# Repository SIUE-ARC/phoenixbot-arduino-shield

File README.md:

# phoenixbot-arduino-shield
Arduino Shield Firmware

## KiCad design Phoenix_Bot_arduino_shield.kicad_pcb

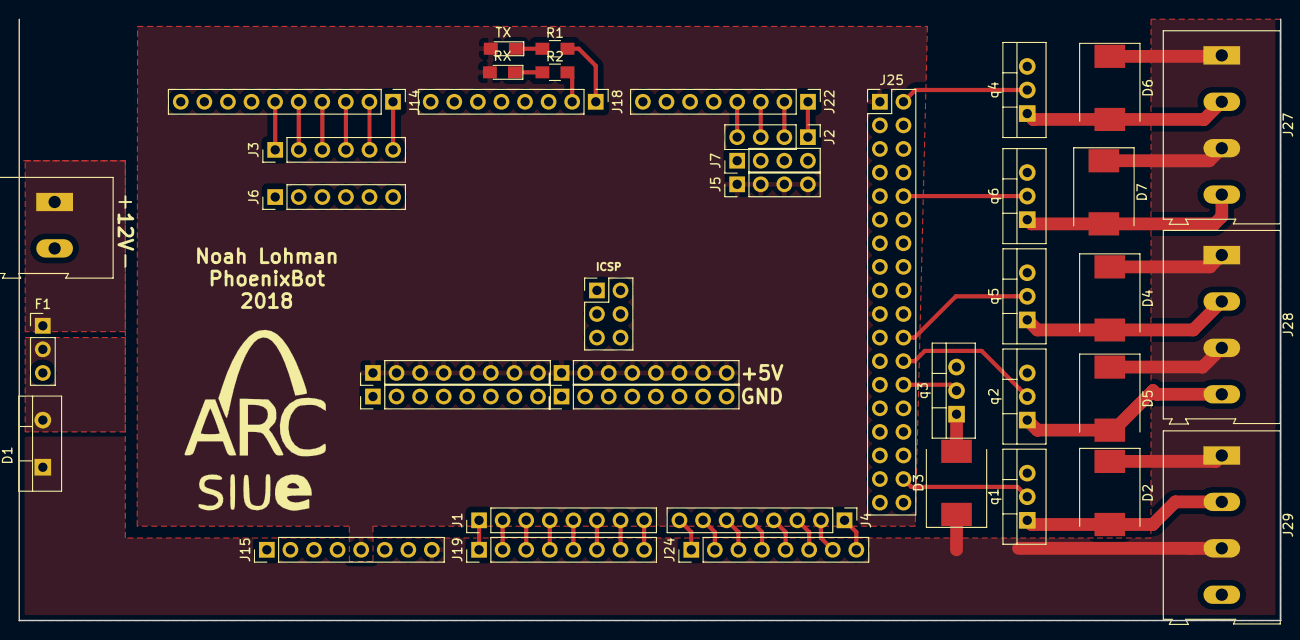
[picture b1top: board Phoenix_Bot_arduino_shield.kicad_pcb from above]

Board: 2 copper layers, 135.9 x 64.8 mm, 41 parts (0 on the bottom side), 48 nets.

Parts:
D1: D_Schottky; TO-220-2_Vertical
D2, D3, D4, D5, D6, D7: D_Schottky; D_SMC
D8: RX; LED_0805_HandSoldering
D9: TX; LED_0805_HandSoldering
F1: Fuse; Pin_Header_Straight_1x03_Pitch2.54mm
J1: Analog_signal_male; Pin_Header_Straight_1x08_Pitch2.54mm
J2: Encoder_Signal; Pin_Header_Straight_1x04_Pitch2.54mm
J3: Servo_signal; Pin_Header_Straight_1x06_Pitch2.54mm
J4: Analog_signal_female; Pin_Header_Straight_1x08_Pitch2.54mm
J5: encoder_power; Pin_Header_Straight_1x04_Pitch2.54mm
J6: Servo_ground; Pin_Header_Straight_1x06_Pitch2.54mm
J7: encoder_ground; Pin_Header_Straight_1x04_Pitch2.54mm
J8: 12V_terminal; TerminalBlock_Altech_AK300-2_P5.00mm
J14: PWN(10-5); Pin_Header_Straight_1x10_Pitch2.54mm
J15: On Board Supply; Pin_Header_Straight_1x08_Pitch2.54mm
J16, J17: 1x8 Male; Pin_Header_Straight_1x08_Pitch2.54mm
J18: PWM_(6-1); Pin_Header_Straight_1x08_Pitch2.54mm
J19: Analog_Pin_1; Pin_Header_Straight_1x08_Pitch2.54mm
J20, J21: 1x8 Female; Pin_Header_Straight_1x08_Pitch2.54mm
J22: Serial; Pin_Header_Straight_1x08_Pitch2.54mm
J23: ICSP; Pin_Header_Straight_2x03_Pitch2.54mm
J24: Analog_Pin_2; Pin_Header_Straight_1x08_Pitch2.54mm
J25: Digital_Pins; Pin_Header_Straight_2x18_Pitch2.54mm
J27: Solenoid_terminal; TerminalBlock_Altech_AK300-4_P5.00mm
J28: Solendoid_middle_terminal; TerminalBlock_Altech_AK300-4_P5.00mm
J29: bottom_solenoid_terminal; TerminalBlock_Altech_AK300-4_P5.00mm
R1, R2: R; R_0805_HandSoldering
q1: solenoid_1; TO-220-3_Vertical
q2: solenoid_4; TO-220-3_Vertical
q3, q5: solenoid_3; TO-220-3_Vertical
q4: solenoid_5; TO-220-3_Vertical
q6: solenoid_6; TO-220-3_Vertical

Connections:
+5V: D8.2, D9.2, J5.1, J5.2, J5.3, J5.4, J15.5, J17.1, J17.2, J17.3, J17.4, J17.5, J17.6, J17.7, J17.8, J20.1, J20.2, J20.3, J20.4, J20.5, J20.6, J20.7, J20.8, J25.1, J25.19
+12V: D1.1, D2.1, D3.1, D4.1, D5.1, D6.1, D7.1, J15.8, J27.1, J27.3, J28.1, J28.3, J29.1, J29.3
/Analog_1: J1.1, J19.1
/Analog_2: J1.2, J19.2
/Analog_3: J1.3, J19.3
/Analog_4: J1.4, J19.4
/Analog_5: J1.5, J19.5
/Analog_6: J1.6, J19.6
/Analog_7: J1.7, J19.7
/Analog_8: J1.8, J19.8
/Analog_9: J4.8, J24.1
/Analog_10: J4.7, J24.2
/Analog_11: J4.6, J24.3
/Analog_12: J4.5, J24.4
/Analog_13: J4.4, J24.5
/Analog_14: J4.3, J24.6
/Analog_15: J4.2, J24.7
/Analog_16: J4.1, J24.8
/Ctrl_1: J25.34, q1.2
/Ctrl_2: J25.26, q3.2
/Ctrl_3: J25.22, q5.2
/Ctrl_4: J25.24, q2.2
/Ctrl_5: J25.2, q4.2
/Ctrl_6: J25.10, q6.2
/Drain_1: D2.2, J29.2, q1.1
/Drain_2: D3.2, J29.4, q3.1
/Drain_3: D4.2, J28.2, q5.1
/Drain_4: D5.2, J28.4, q2.1
/Drain_5: D6.2, J27.2, q4.1
/Drain_6: D7.2, J27.4, q6.1
/Encoder_1: J2.1, J22.1
/Encoder_2: J2.2, J22.2
/Encoder_3: J2.3, J22.3
/Encoder_4: J2.4, J22.4
/RX: J18.2, R2.2
/Reset: J15.3, J23.5
/Servo_1: J3.1, J14.6
/Servo_2: J3.2, J14.5
/Servo_3: J3.3, J14.4
/Servo_4: J3.4, J14.3
/Servo_5: J3.5, J14.2
/Servo_6: J3.6, J14.1
/TX: J18.1, R1.2
GND: J6.1, J6.2, J6.3, J6.4, J6.5, J6.6, J7.1, J7.2, J7.3, J7.4, J8.2, J14.7, J15.6, J15.7, J16.1, J16.2, J16.3, J16.4, J16.5, J16.6, J16.7, J16.8, J21.1, J21.2, J21.3, J21.4, J21.5, J21.6, J21.7, J21.8, J23.6, J25.18, J25.36, q1.3, q2.3, q3.3, q4.3, q5.3, q6.3
unnamed: D1.2, F1.2
unnamed: D8.1, R2.1
unnamed: D9.1, R1.1
unnamed: F1.1, J8.1

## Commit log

2018-02-09 Started schematic and started pcb block
2018-02-10 Updated the Schematic with solenoids
2018-02-11 Updated the Schematic with Analog mapping, encoder, solenoid, and servo
2018-02-11 Added ICSP mapping
2018-02-12 Finished schematic and laid out PCB design
2018-02-12 Fixed hole alignment and pin count issues
2018-02-13 Began board layout
2018-02-13 More progress on Board, mapped except solenoids
2018-02-13 Added .gitignore, rescued old PCB file. Cleaned up repo to match .gitignore settings.
2018-02-13 Removed tracked .net files. .net files can be regenerated locally.
2018-02-13 Removed autosave files. Autosaves should be kept local and used for recovery purposes.
2018-02-13 Fixed issues porting from mac and started solenoid wiring
2018-02-13 Added my name, and finished solenoid mapping
2018-02-13 Started Bill Of Materials for PhoenixBot
2018-02-14 Board design finished. Final review needed.
2018-02-14 Finished BOM
2018-02-17 added etching files
2018-02-17 Added svg
2018-02-17 Changed to 18 mil tracks for signals and 24 mil clearance to allow for easier etching.
2018-02-24 Added resized copper mask so it can be immediately printed on computer paper
2019-01-25 added pinout of shield
2019-01-25 added shield pin out
